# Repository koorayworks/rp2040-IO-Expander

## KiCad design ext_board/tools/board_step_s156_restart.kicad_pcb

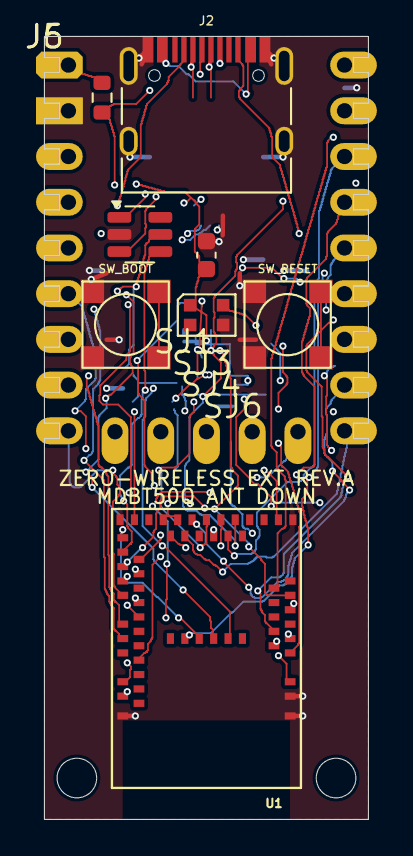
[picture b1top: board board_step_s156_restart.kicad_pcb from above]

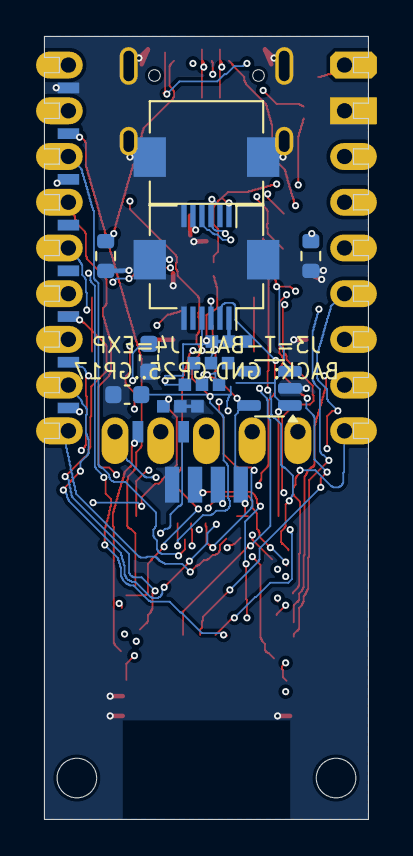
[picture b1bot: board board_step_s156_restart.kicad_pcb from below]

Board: 4 copper layers, 18.0 x 43.5 mm, 24 parts (11 on the bottom side), 54 nets.

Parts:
C1: 10uF IN; C_0603_1608Metric
C2: 10uF OUT; C_0603_1608Metric
C3: 100nF; C_0603_1608Metric
D1: USBLC6-2SC6; SOT-23-6
D2: WS2812B-2020; LED_WS2812B-2020_PLCC4_2.0x2.0mm
J2: TYPE-C-31-M-12
J3: FFC6 TB; Hirose_FH12-6S-0.5SH_1x06-1MP_P0.50mm_Horizontal
J4: FFC6 EXP; Hirose_FH12-6S-0.5SH_1x06-1MP_P0.50mm_Horizontal
J5: SWD
J6: BACKPADS GP17-25
JLEG: RP2040-Zero-THT; RP2040-Zero-THT-Castellation-Master
MH1, MH2: M2; MountingHole_2.2mm_M2
R1: 5.1k CC1; R_0603_1608Metric
R2: 5.1k CC2; R_0603_1608Metric
R3: 0R VBUS->VSYS; R_0603_1608Metric
SJ1, SJ3, SJ4, SJ6: SJ
SW_BOOT: TS-1187A-B-A-B / C318884; SW-SMD_4P-L5.1-W5.1-P3.70-LS6.5-TL_H1.5
SW_RESET: TS-1187A-B-A-B / C318884; SW-SMD_4P-L5.1-W5.1-P3.70-LS6.5-TL_H1.5
U1: MDBT50Q-1MV2; MDBT50Q
U2: TPS7A2033PDBVR; SOT-23-5

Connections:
3V3: C2.1, C3.1, D2.1, J3.1, J4.1, J5.1, JLEG.30, SJ1.2, SJ1.3, SJ4.3, U1.28, U1.30, U2.5
BOOT: SW_BOOT.2, SW_BOOT.3, U1.14
CC1: J2.A5, R1.1
CC2: J2.B5, R2.1
EX1: SJ1.1, U1.48
EX2: J4.2, U1.49
EX3: J4.3, SJ3.1, SJ3.2, U1.50
EX4: J4.4, SJ4.1, SJ4.2, U1.47
EX5: J4.5, U1.19
EX6: SJ6.3, U1.10
GND: C1.2, C2.2, C3.2, D1.2, D2.3, J2.A1, J2.A12, J2.B1, J2.B12, J2.S1, J3.6, J3.MP, J4.6, J4.MP, J5.4, J6.1, JLEG.31, R1.2, R2.2, SJ3.3, SJ6.1, SJ6.2, SW_BOOT.1, SW_BOOT.4, SW_RESET.1, SW_RESET.4, U1.1, U1.2, U1.15, U1.33, U1.55, U2.2
GP17: J6.10, U1.3
GP18: J6.9, U1.4
GP19: J6.8, U1.5
GP20: J6.7, U1.6
GP21: J6.6, U1.7
GP22: J6.5, U1.8
GP23: J6.4, U1.11
GP24: J6.3, U1.12
GP25: J6.2, U1.13
GPIO0: JLEG.0, U1.9
GPIO1: JLEG.1, U1.20
GPIO2: JLEG.2, U1.21
GPIO3: JLEG.3, U1.22
GPIO4: JLEG.4, U1.23
GPIO5: JLEG.5, U1.24
GPIO6: JLEG.6, U1.25
GPIO7: JLEG.7, U1.26
GPIO8: JLEG.8, U1.27
GPIO9: JLEG.9, U1.29
GPIO10: JLEG.10, U1.37
GPIO11: JLEG.11, U1.36
GPIO12: JLEG.12, U1.39
GPIO13: JLEG.13, U1.38
GPIO14: JLEG.14, U1.41
GPIO15: JLEG.15, U1.42
GPIO26: JLEG.26, U1.44
GPIO27: JLEG.27, U1.43
GPIO28: JLEG.28, U1.46
GPIO29: JLEG.29, U1.45
RESET: SW_RESET.2, SW_RESET.3, U1.40
STATUS_LED: D2.4, U1.16
SWDCLK: J5.3, U1.53
SWDIO: J5.2, U1.51
TB2: J3.2, U1.57
TB3: J3.3, U1.58
TB4: J3.4, U1.59
TB5: J3.5, U1.60
USB_D+: D1.4, U1.35
USB_D+_C: D1.3, J2.A6, J2.B6
USB_D-: D1.6, U1.34
USB_D-_C: D1.1, J2.A7, J2.B7
USB_VBUS: C1.1, D1.5, J2.A4, J2.A9, J2.B4, J2.B9, R3.1, U1.32, U2.1, U2.3
VSYS: JLEG.32, R3.2
